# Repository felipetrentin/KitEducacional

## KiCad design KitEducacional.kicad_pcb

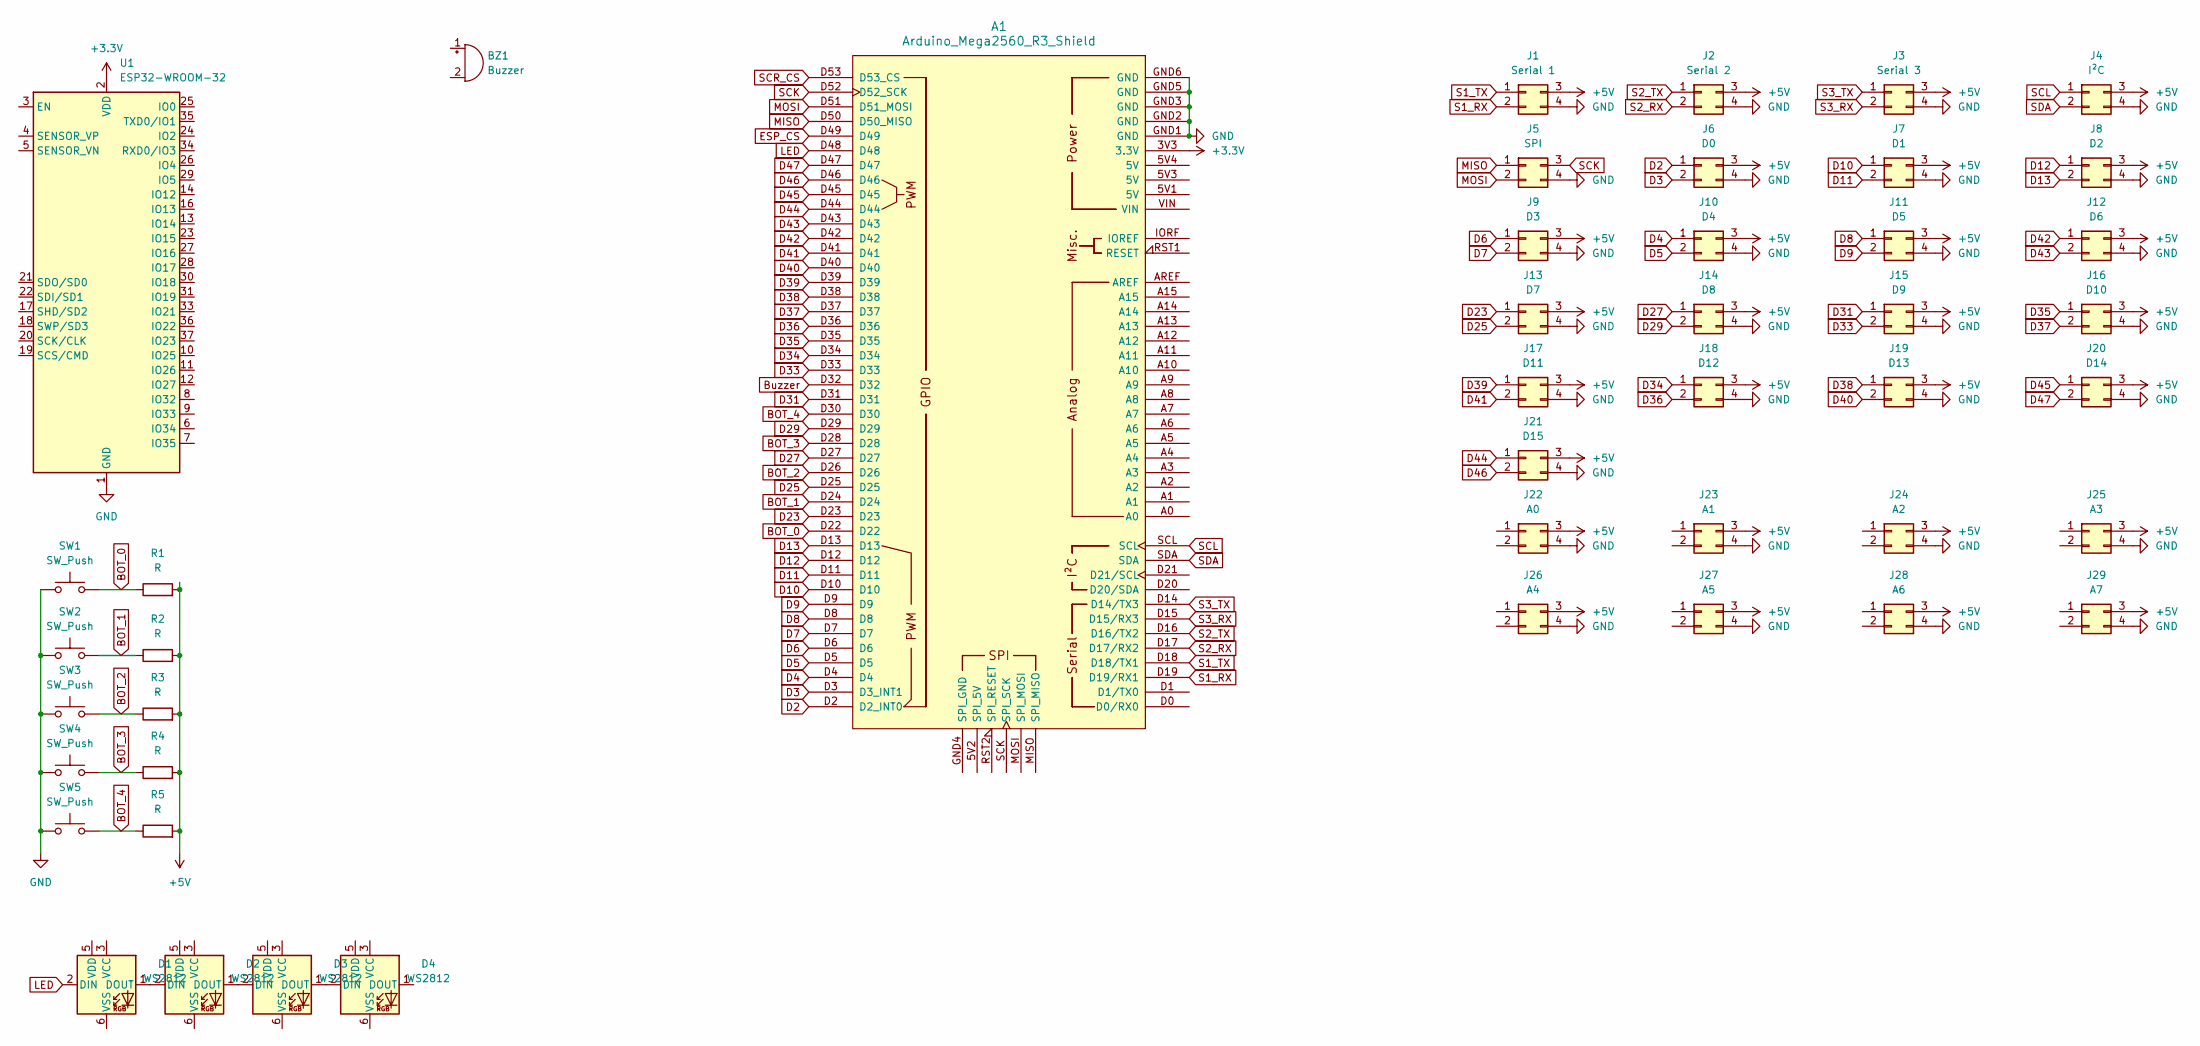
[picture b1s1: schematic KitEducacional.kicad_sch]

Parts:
A1: Arduino_Mega2560_R3_Shield
BZ1: Buzzer; Buzzer_12x9.5RM7.6
D1, D2, D3, D4: WS2812; LED_WS2812_PLCC6_5.0x5.0mm_P1.6mm
J1: Serial 1; Molex_Mini-Fit_Jr_5569-04A2_2x02_P4.20mm_Horizontal
J2: Serial 2; Molex_Mini-Fit_Jr_5569-04A2_2x02_P4.20mm_Horizontal
J3: Serial 3; Molex_Mini-Fit_Jr_5569-04A2_2x02_P4.20mm_Horizontal
J4: I²C; Molex_Mini-Fit_Jr_5569-04A2_2x02_P4.20mm_Horizontal
J5: SPI; Molex_Mini-Fit_Jr_5569-04A2_2x02_P4.20mm_Horizontal
J6: D0; Molex_Mini-Fit_Jr_5569-04A2_2x02_P4.20mm_Horizontal
J7: D1; Molex_Mini-Fit_Jr_5569-04A2_2x02_P4.20mm_Horizontal
J8: D2; Molex_Mini-Fit_Jr_5569-04A2_2x02_P4.20mm_Horizontal
J9: D3; Molex_Mini-Fit_Jr_5569-04A2_2x02_P4.20mm_Horizontal
J10: D4; Molex_Mini-Fit_Jr_5569-04A2_2x02_P4.20mm_Horizontal
J11: D5; Molex_Mini-Fit_Jr_5569-04A2_2x02_P4.20mm_Horizontal
J12: D6; Molex_Mini-Fit_Jr_5569-04A2_2x02_P4.20mm_Horizontal
J13: D7; Molex_Mini-Fit_Jr_5569-04A2_2x02_P4.20mm_Horizontal
J14: D8; Molex_Mini-Fit_Jr_5569-04A2_2x02_P4.20mm_Horizontal
J15: D9; Molex_Mini-Fit_Jr_5569-04A2_2x02_P4.20mm_Horizontal
J16: D10; Molex_Mini-Fit_Jr_5569-04A2_2x02_P4.20mm_Horizontal
J17: D11; Molex_Mini-Fit_Jr_5569-04A2_2x02_P4.20mm_Horizontal
J18: D12; Molex_Mini-Fit_Jr_5569-04A2_2x02_P4.20mm_Horizontal
J19: D13; Molex_Mini-Fit_Jr_5569-04A2_2x02_P4.20mm_Horizontal
J20: D14; Molex_Mini-Fit_Jr_5569-04A2_2x02_P4.20mm_Horizontal
J21: D15; Molex_Mini-Fit_Jr_5569-04A2_2x02_P4.20mm_Horizontal
J22: A0; Molex_Mini-Fit_Jr_5569-04A2_2x02_P4.20mm_Horizontal
J23: A1; Molex_Mini-Fit_Jr_5569-04A2_2x02_P4.20mm_Horizontal
J24: A2; Molex_Mini-Fit_Jr_5569-04A2_2x02_P4.20mm_Horizontal
J25: A3; Molex_Mini-Fit_Jr_5569-04A2_2x02_P4.20mm_Horizontal
J26: A4; Molex_Mini-Fit_Jr_5569-04A2_2x02_P4.20mm_Horizontal
J27: A5; Molex_Mini-Fit_Jr_5569-04A2_2x02_P4.20mm_Horizontal
J28: A6; Molex_Mini-Fit_Jr_5569-04A2_2x02_P4.20mm_Horizontal
J29: A7; Molex_Mini-Fit_Jr_5569-04A2_2x02_P4.20mm_Horizontal
R1, R2, R3, R4, R5: R; R_0805_2012Metric
SW1, SW2, SW3, SW4, SW5: SW_Push; SW_PUSH_6mm
U1: ESP32-WROOM-32

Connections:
+3.3V: A1.3V3 (3.3V), U1.2 (VDD)
+5V: J1.3, J2.3, J3.3, J4.3, J6.3, J7.3, J8.3, J9.3, J10.3, J11.3, J12.3, J13.3, J14.3, J15.3, J16.3, J17.3, J18.3, J19.3, J20.3, J21.3, J22.3, J23.3, J24.3, J25.3, J26.3, J27.3, J28.3, J29.3, R1.2, R2.2, R3.2, R4.2, R5.2
BOT_0: A1.D22, R1.1, SW1.2
BOT_1: A1.D24, R2.1, SW2.2
BOT_2: A1.D26, R3.1, SW3.2
BOT_3: A1.D28, R4.1, SW4.2
BOT_4: A1.D30, R5.1, SW5.2
Buzzer: A1.D32
D2: A1.D2 (D2_INT0), J6.1
D3: A1.D3 (D3_INT1), J6.2
D4: A1.D4, J10.1
D5: A1.D5, J10.2
D6: A1.D6, J9.1
D7: A1.D7, J9.2
D8: A1.D8, J11.1
D9: A1.D9, J11.2
D10: A1.D10, J7.1
D11: A1.D11, J7.2
D12: A1.D12, J8.1
D13: A1.D13, J8.2
D23: A1.D23, J13.1
D25: A1.D25, J13.2
D27: A1.D27, J14.1
D29: A1.D29, J14.2
D31: A1.D31, J15.1
D33: A1.D33, J15.2
D34: A1.D34, J18.1
D35: A1.D35, J16.1
D36: A1.D36, J18.2
D37: A1.D37, J16.2
D38: A1.D38, J19.1
D39: A1.D39, J17.1
D40: A1.D40, J19.2
D41: A1.D41, J17.2
D42: A1.D42, J12.1
D43: A1.D43, J12.2
D44: A1.D44, J21.1
D45: A1.D45, J20.1
D46: A1.D46, J21.2
D47: A1.D47, J20.2
ESP_CS: A1.D49
GND: A1.GND1 (GND), A1.GND2 (GND), A1.GND3 (GND), A1.GND5 (GND), A1.GND6 (GND), J1.4, J2.4, J3.4, J4.4, J5.4, J6.4, J7.4, J8.4, J9.4, J10.4, J11.4, J12.4, J13.4, J14.4, J15.4, J16.4, J17.4, J18.4, J19.4, J20.4, J21.4, J22.4, J23.4, J24.4, J25.4, J26.4, J27.4, J28.4, J29.4, SW1.1, SW2.1, SW3.1, SW4.1, SW5.1, U1.1 (GND), U1.15 (GND), U1.38 (GND), U1.39 (GND)
LED: A1.D48, D1.2 (DIN)
MISO: A1.D50 (D50_MISO), J5.1
MOSI: A1.D51 (D51_MOSI), J5.2
unnamed: D1.1 (DOUT), D2.2 (DIN)
unnamed: D2.1 (DOUT), D3.2 (DIN)
unnamed: D3.1 (DOUT), D4.2 (DIN)
S1_RX: A1.D19 (D19/RX1), J1.2
S1_TX: A1.D18 (D18/TX1), J1.1
S2_RX: A1.D17 (D17/RX2), J2.2
S2_TX: A1.D16 (D16/TX2), J2.1
S3_RX: A1.D15 (D15/RX3), J3.2
S3_TX: A1.D14 (D14/TX3), J3.1
SCK: A1.D52 (D52_SCK), J5.3
SCL: A1.SCL, J4.1
SCR_CS: A1.D53 (D53_CS)
SDA: A1.SDA, J4.2

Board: 2 copper layers, 46 parts (30 on the bottom side), 55 nets, no tracks yet.

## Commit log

2024-01-14 add components to board
2024-01-14 go back to molex Nano Fit
2024-01-16 goto mini-fit
